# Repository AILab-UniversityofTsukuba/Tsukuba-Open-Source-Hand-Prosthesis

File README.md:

# Tsukuba-Hand-Prosthesis-Open-Source

Currently, myoelectric hand prostheses present physical and control challenges that hinder their effective use by children with unilateral congenital below-elbow deficiency (UCBED).
In the Artificial Intelligence Laboratory at the University of Tsukuba, we conducted an investigation to address some of these challenges. 
Regarding the physical challenges, we focused on excessive weight, lack of hand size adaptability, and lack of socket size adaptability.
As for the control challenges, our focus was on the uncertain EMG measurement, absence of sensory feedback, and challenging EMG training.

To find clinically feasible solutions for these challenges, we proposed developing a myoelectric hand prosthesis for children with UCBED under personalized and modular design approaches.
We proposed a personalized approach to involve children in the design process, finding out and meeting the children’s unique needs regarding myoelectric prosthetic hands to facilitate its adoption.
While, we adopted a modular approach to divide the prosthesis into interchangeable modules, providing flexibility to update the modules to adapt to children's developmental growth.
Both approaches were applied to all levels of the design of the prosthesis.

Results show that the developed myoelectric prosthesis presents potential solutions for the mentioned challenges.
As an outcome of the study and synthesis of the personalized and modular design approaches, the developed hand prosthesis, including the proposed solutions, are shared as open-source material. 
Thus, children have free access to a myoelectric hand prosthesis that can be customized to suit their evolving growth patterns and personal preferences.
Furthermore, thanks to their modularity, the prosthesis's modules can be interchanged and used with other prostheses, such as controlling a specific-activity prosthesis while using our proposed prosthesis interface.

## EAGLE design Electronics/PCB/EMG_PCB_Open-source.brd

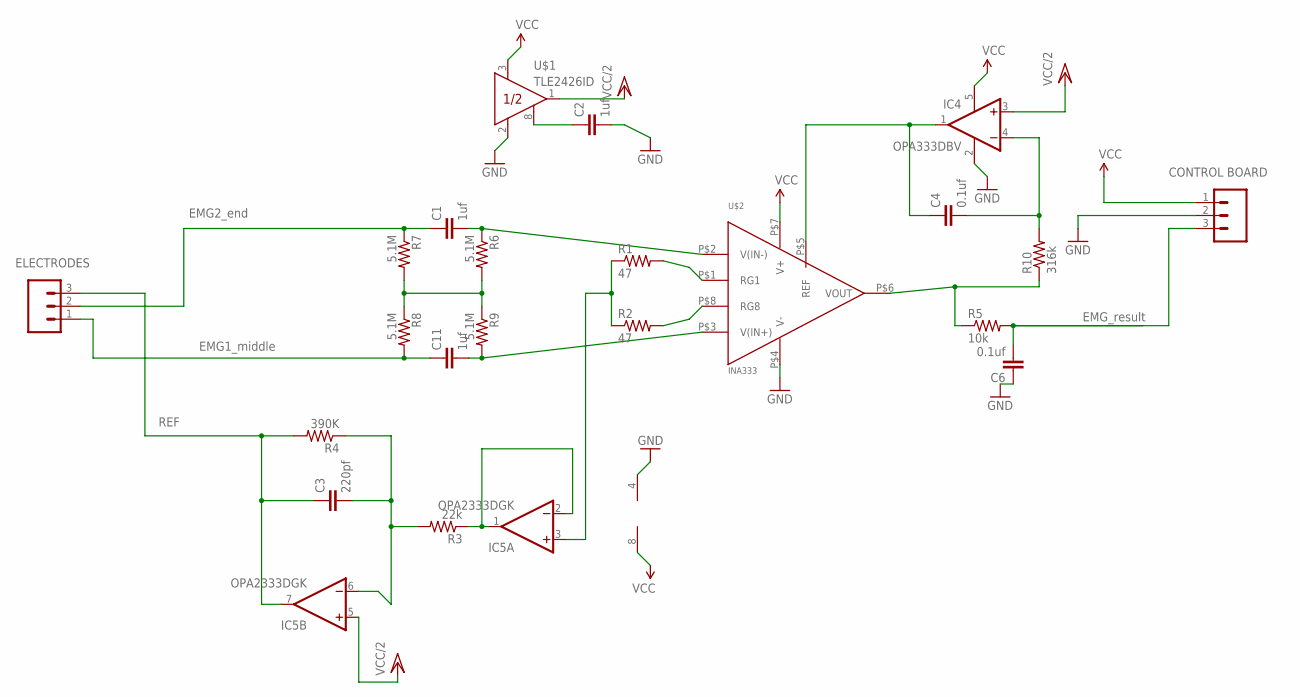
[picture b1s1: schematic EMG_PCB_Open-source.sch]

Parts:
C1, C2, C11: 1uf; C0603
C3: 220pf; C0603
C4, C6: 0.1uf; C0603
IC4: OPA333DBV; SOT23-5
IC5: OPA2333DGK; MSOP08
J1, J2: 455-1750-1-ND; 1X03
R1, R2: 47; R0603
R3: 22k; R0603
R4: 390K; 0603-RES
R5: 10k; R0603
R6, R7, R8, R9: 5.1M; 0603-RES
R10: 316k; R0603
U$1: TLE2426ID; SO-8
U$2: INA333; 8-MSOP

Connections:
ADC0: C6.2, J2.3, R5.2
GND: C2.2, C6.1, IC4.2 (V-), IC5.4 (V-), J2.2, U$1.2 (COM), U$2.P$4 (V-)
unnamed: R1.2, U$2.P$1 (RG1)
unnamed: R2.2, U$2.P$8 (RG8)
unnamed: C1.1, J1.2, R7.1
unnamed: R6.2, R7.2, R8.1, R9.1
unnamed: C1.2, R6.1, U$2.P$2 (V(IN-))
unnamed: C11.2, R9.2, U$2.P$3 (V(IN+))
unnamed: C11.1, J1.1, R8.2
unnamed: IC5.3 (+IN), R1.1, R2.1
unnamed: C2.1, U$1.8 (NR)
unnamed: C3.2, IC5.6 (-IN), R3.2, R4.1
unnamed: C3.1, IC5.7 (OUT), J1.3, R4.2
unnamed: C4.2, IC4.4 (-IN), R10.2
unnamed: C4.1, IC4.1 (OUT), U$2.P$5 (REF)
unnamed: IC5.1 (OUT), IC5.2 (-IN), R3.1
unnamed: R5.1, R10.1, U$2.P$6 (VOUT)
VCC: IC4.5 (V+), IC5.8 (V+), J2.1, U$1.3 (IN), U$2.P$7 (V+)
VCC/2: IC4.3 (+IN), IC5.5 (+IN), U$1.1 (OUT)

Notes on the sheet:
EMG2_end
EMG1_middle
REF
EMG_result
ELECTRODES
CONTROL BOARD

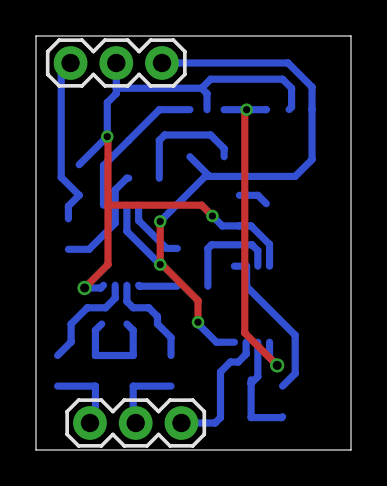
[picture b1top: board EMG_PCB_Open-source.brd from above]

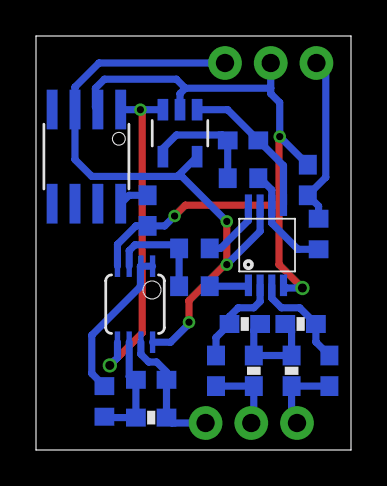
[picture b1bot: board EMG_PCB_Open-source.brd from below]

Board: 2 copper layers, 17.5 x 23.0 mm, 22 parts (20 on the bottom side), 19 nets.

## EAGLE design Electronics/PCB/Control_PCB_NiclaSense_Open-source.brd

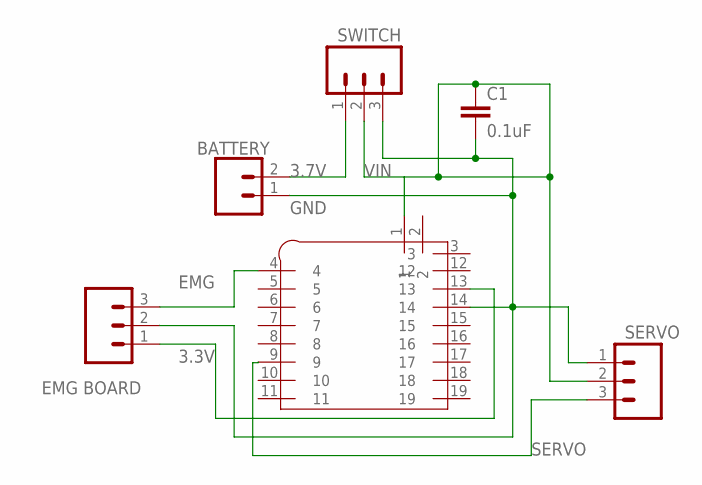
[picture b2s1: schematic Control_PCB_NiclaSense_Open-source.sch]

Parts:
BATTERY: CONN_02JST-PTH-2; JST-2-PTH
C1: 0.1uF; C0603K
J2, J3: 455-1750-1-ND; 1X03
SD: sadasd; 1X03
U$1: ARDUINO_NICLA

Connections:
3.3V: SD.1, U$1.13
3.7V: BATTERY.2, J3.1
EMG: SD.3, U$1.4
GND: BATTERY.1, C1.2, J2.1, J3.3, SD.2, U$1.14
SERVO: J2.3, U$1.9
VIN: C1.1, J2.2, J3.2, U$1.1

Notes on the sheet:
EMG BOARD
SERVO
SWITCH

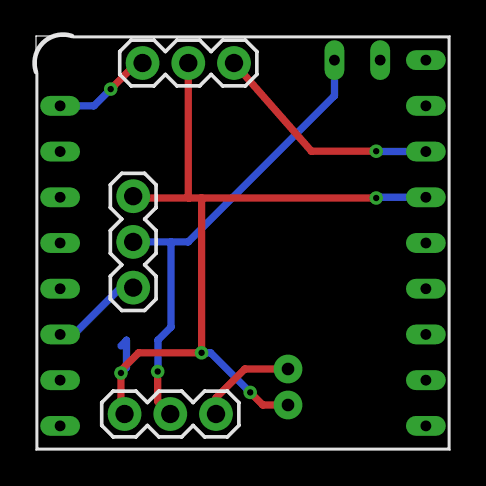
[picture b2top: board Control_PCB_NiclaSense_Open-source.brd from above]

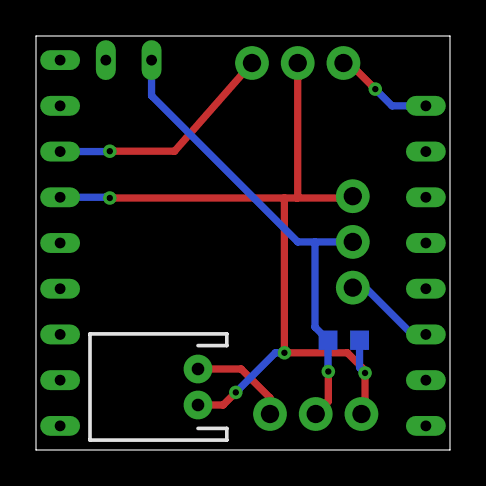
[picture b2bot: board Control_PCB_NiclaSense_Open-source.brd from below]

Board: 2 copper layers, 23.0 x 23.0 mm, 6 parts (2 on the bottom side), 6 nets.

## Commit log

2024-01-22 Create Electronics
2024-01-22 Create asdf
2024-01-22 Create fsd
2024-01-23 Create asdfasd
2024-01-23 Create asdfds
2024-01-23 Create asd
2024-01-23 Create sadas
2024-01-23 Create CAM files
2024-01-23 Create dfsdf
2024-01-23 Create df
2024-01-23 Create sadf
2024-01-24 Create sdf
2024-01-24 Create sdfdf

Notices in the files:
parts and their libraries:
SparkFun-Connectors: Licensing: Creative Commons ShareAlike 4.0 International - https://creativecommons.org/licenses/by-sa/4.0
SparkFun: Licensing: CC v3.0 Share-Alike You are welcome to use this library for commercial purposes.
